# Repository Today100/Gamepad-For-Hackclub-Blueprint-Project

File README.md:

# Gamepad - For Hackclub Blueprint Project
A hackpad that can be used to play little mini games. I think it's a fun little thing to use to take a break.

Link to Blueprint: [https://blueprint.hackclub.com/projects/8584](url)

## **Build:**
Demo: [https://youtu.be/U4rZsfkFq84](url)

## **Design:**
BOM:
- 1x XIAO RP2040
- 16x Cherry MX Switches
- 16x Through-hole 1N4148 Diodes
- 16x Blank DSA Keycaps
- 1x SK6812 MINI LEDs
- 1x 0.91 inch OLED displays
- 4x M3x16 Bolt

Pictures:

| Image | Title |
| :---: | :--- |
| | **Overall hackpad**|
| | **Schematic**|
| |**PCB**|
| | **Case**|

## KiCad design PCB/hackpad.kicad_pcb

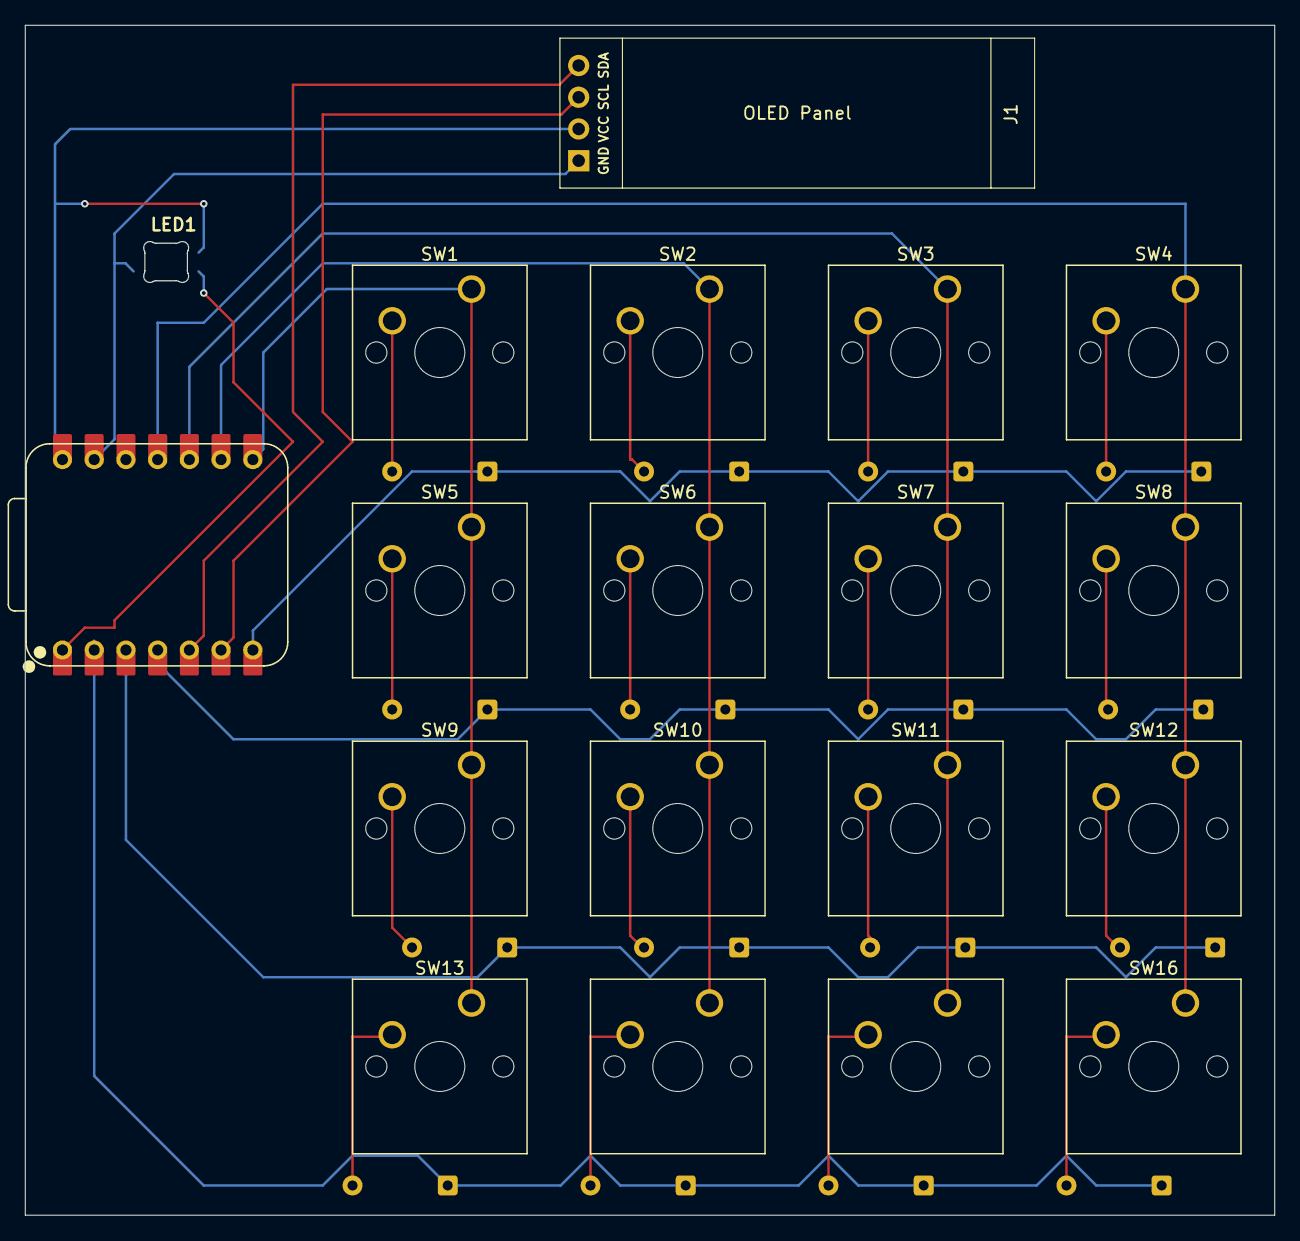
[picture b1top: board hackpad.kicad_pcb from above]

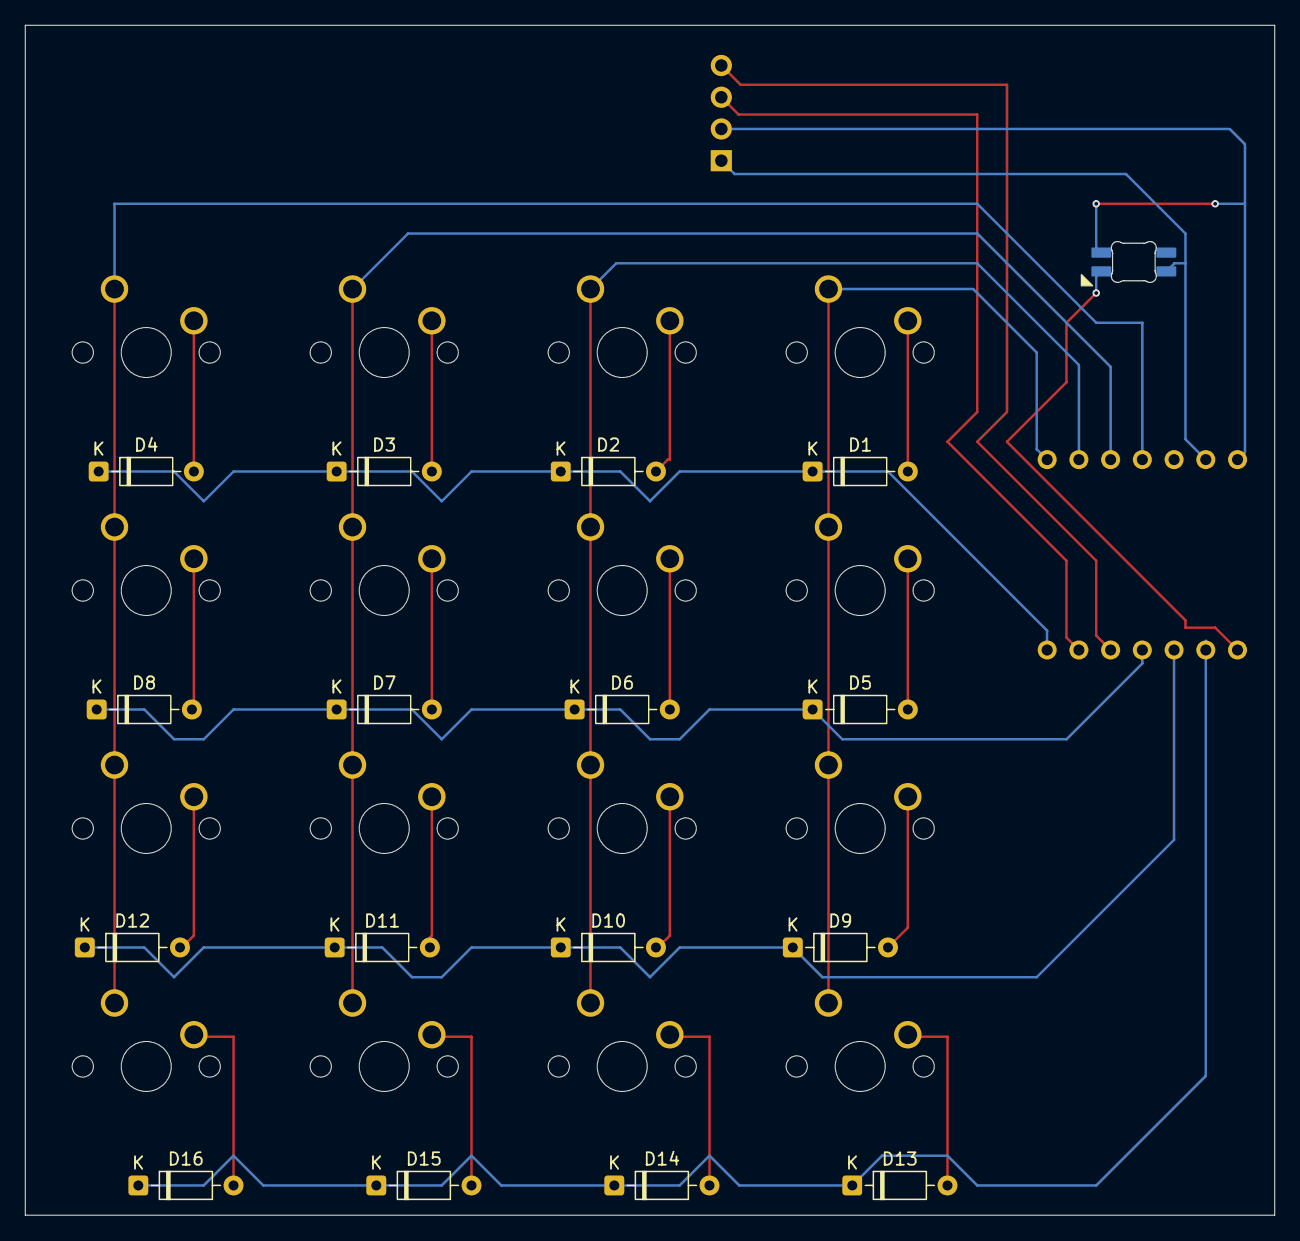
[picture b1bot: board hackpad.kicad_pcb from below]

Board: 2 copper layers, 100.0 x 95.2 mm, 35 parts (16 on the bottom side), 29 nets.

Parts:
D1, D2, D3, D4, D5, D6, D7, D8, D9, D10, D11, D12, D13, D14, D15, D16: 1N4148; D_DO-35_SOD27_P7.62mm_Horizontal
J1: OLED; SSD1306-0.91-OLED-4pin-128x32
LED1: SK6812MINI; SK6812MINI-E_fixed
SW1, SW2, SW3, SW4, SW5, SW6, SW7, SW8, SW9, SW10, SW11, SW12, SW13, SW14, SW15, SW16: SW_Push_45deg; SW_Cherry_MX_1.00u_PCB
U1: XIAO-RP2040-DIP

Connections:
+5V: J1.2, LED1.4 (VDD), U1.14 (VBUS)
GND: J1.1, LED1.2 (VSS), U1.13 (GND)
unnamed: D1.2 (A), SW1.2
unnamed: D1.1 (K), D2.1 (K), D3.1 (K), D4.1 (K), U1.7 (GPIO0/TX)
unnamed: D2.2 (A), SW2.2
unnamed: D3.2 (A), SW3.2
unnamed: D4.2 (A), SW4.2
unnamed: D5.2 (A), SW5.2
unnamed: D5.1 (K), D6.1 (K), D7.1 (K), D8.1 (K), U1.4 (GPIO29/ADC3/A3)
unnamed: D6.2 (A), SW6.2
unnamed: D7.2 (A), SW7.2
unnamed: D8.2 (A), SW8.2
unnamed: D9.2 (A), SW9.2
unnamed: D10.2 (A), SW10.2
unnamed: D9.1 (K), D10.1 (K), D11.1 (K), D12.1 (K), U1.3 (GPIO28/ADC2/A2)
unnamed: D11.2 (A), SW11.2
unnamed: D12.2 (A), SW12.2
unnamed: D13.2 (A), SW13.2
unnamed: D13.1 (K), D14.1 (K), D15.1 (K), D16.1 (K), U1.2 (GPIO27/ADC1/A1)
unnamed: D14.2 (A), SW14.2
unnamed: D15.2 (A), SW15.2
unnamed: D16.2 (A), SW16.2
unnamed: J1.3, U1.6 (GPIO7/SCL)
unnamed: J1.4, U1.5 (GPIO6/SDA)
unnamed: LED1.3 (DIN), U1.1 (GPIO26/ADC0/A0)
unnamed: SW1.1, SW5.1, SW9.1, SW13.1, U1.8 (GPIO1/RX)
unnamed: SW2.1, SW6.1, SW10.1, SW14.1, U1.9 (GPIO2/SCK)
unnamed: SW4.1, SW8.1, SW12.1, SW16.1, U1.11 (GPIO3/MOSI)
unnamed: SW3.1, SW7.1, SW11.1, SW15.1, U1.10 (GPIO4/MISO)

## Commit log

2026-01-11 Added the CAD files
2026-01-11 Rename clock2.step to clock_pcb.step
2026-01-11 Update clock_top.step file
2026-01-11 Add hackpad_bottom.step file
2026-01-11 Rename clock.kicad_pro to hackpad.kicad_pro
2026-01-11 Updated Project Information
    Added specifications and images for the hackpad project.
2026-01-11 Remove specifications from README
    Removed specifications section from README.
2026-01-13 Add hackpad_pcb.step file
2026-01-15 Modification to the symbol and footprint of led
2026-01-15 Update image links and titles in README
2026-01-15 Create placeholder
2026-02-27 Modified Code to work with the final product
2026-03-30 Update README with build link and design details
    Added build link and design BOM to README.
2026-03-30 Add Blueprint link to README
    Added a link to the Blueprint for the project.
2026-03-30 Update README with project introduction and links
    Added a brief introduction and a link to the project blueprint.
2026-03-30 Update demo link in README
